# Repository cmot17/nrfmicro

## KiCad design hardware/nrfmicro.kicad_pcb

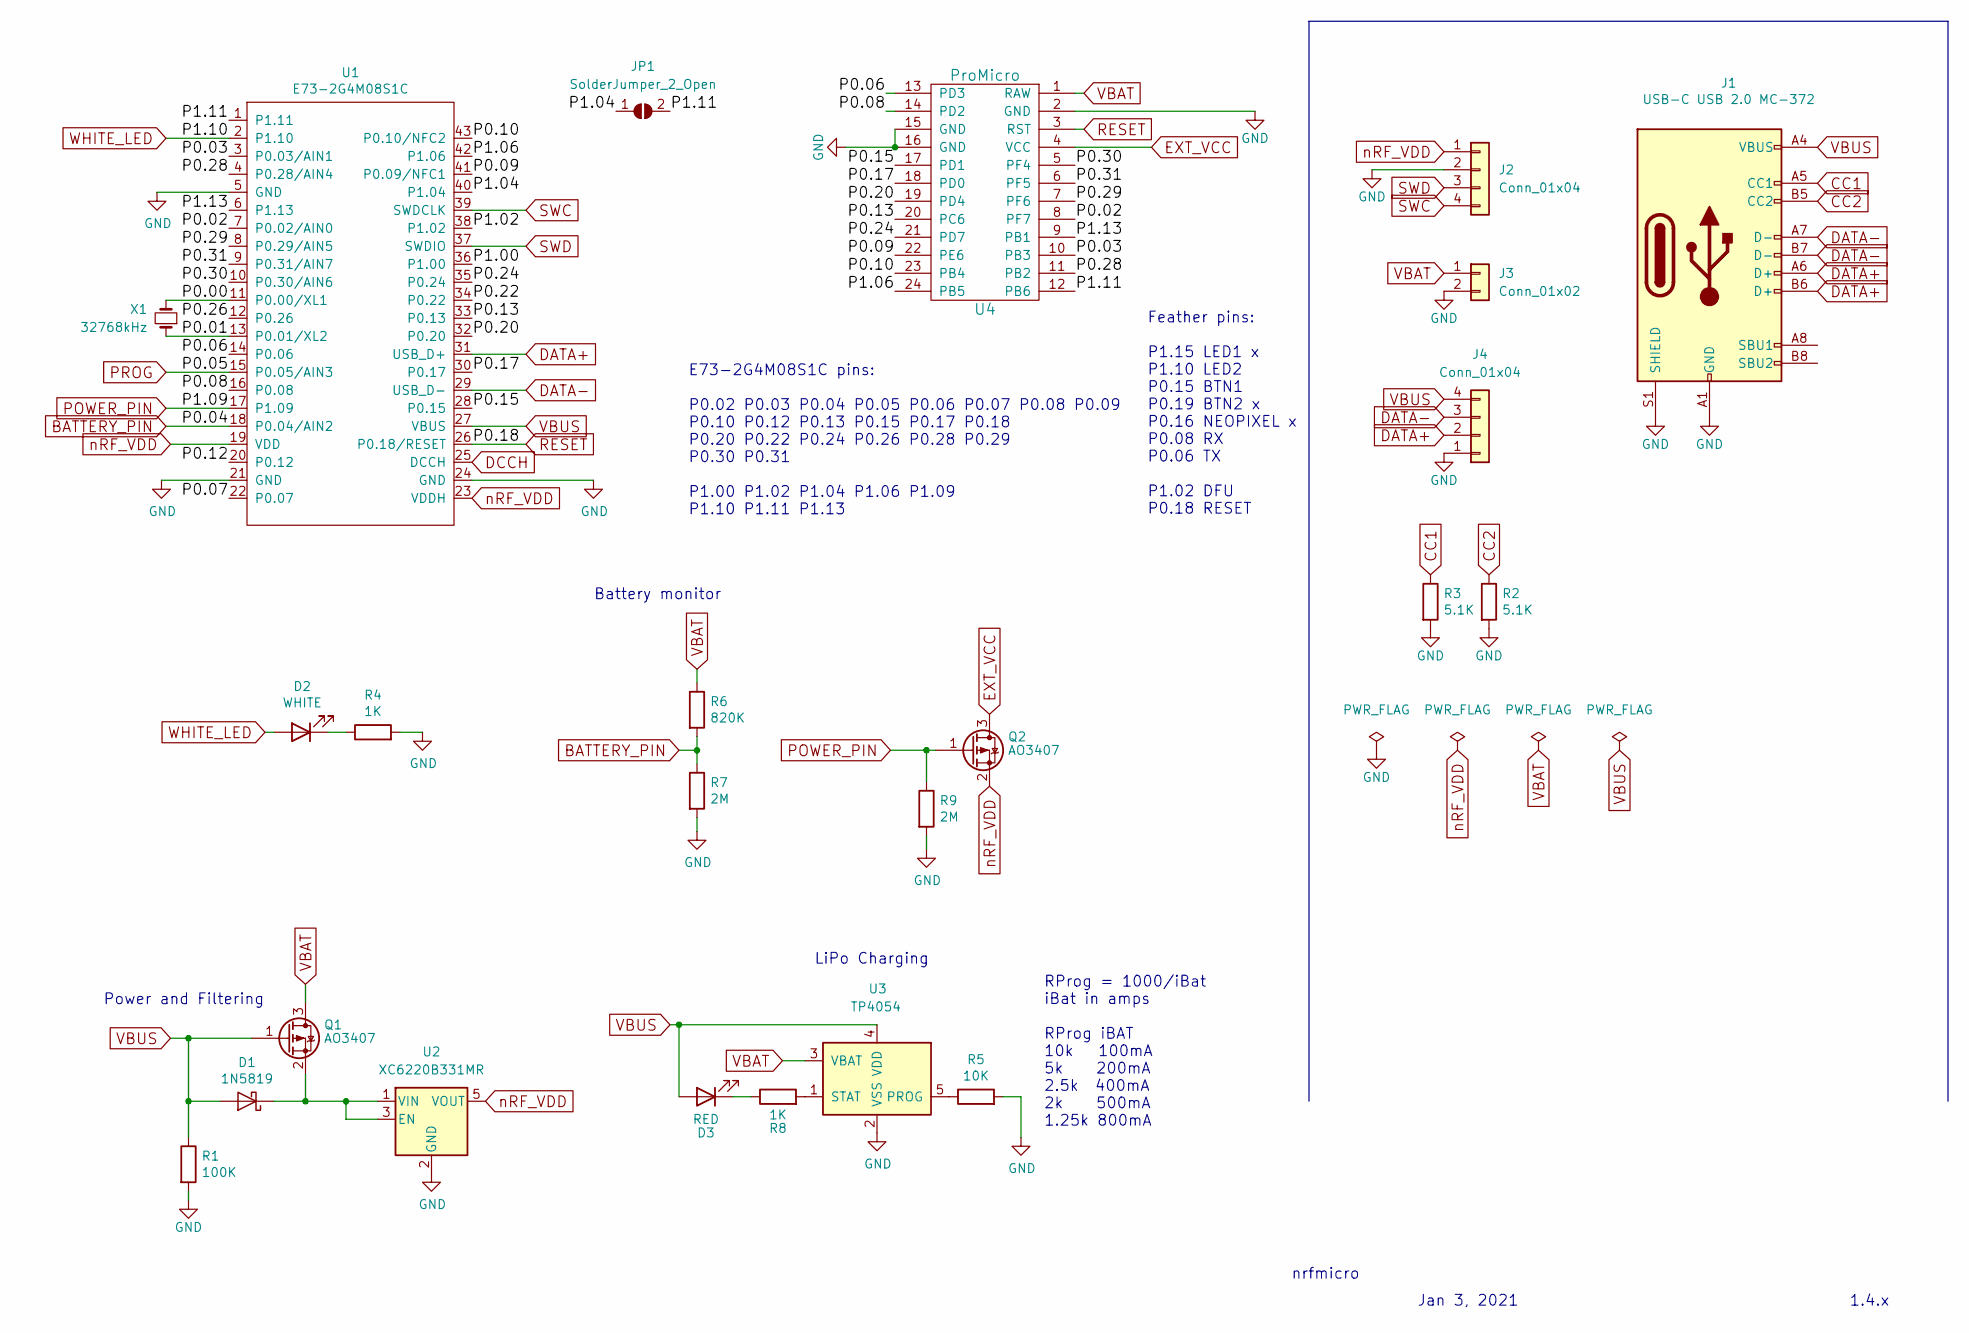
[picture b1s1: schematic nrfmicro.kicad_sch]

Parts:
D1: 1N5819; D_SOD-323F
D2: WHITE; LED_0603_1608Metric; LCSC C2290
D3: RED; LED_0603_1608Metric; LCSC C2286
J1: USB-C USB 2.0 MC-372; GT-USB-7047B; LCSC C963217
J2: Conn_01x04; connector_swd
J3: Conn_01x02; connector_bat
J4: Conn_01x04; connector_usb
JP1: SolderJumper_2_Open; Jumper_SMD
Q1, Q2: AO3407; SOT-23; JLCPCB Rotation Offset 180
R1: 100K; R_0402_1005Metric
R2, R3: 5.1K; R_0402_1005Metric
R4, R8: 1K; R_0402_1005Metric
R5: 10K; R_0402_1005Metric
R6: 820K; R_0402_1005Metric
R7, R9: 2M; R_0402_1005Metric
U1: E73-2G4M08S1C; E73-2G4M08S1C-52840
U2: XC6220B331MR; SOT-23-5; LCSC C86534
U3: TP4054; SOT-23-5; JLCPCB Rotation Offset 180
U4: ProMicro; pro_micro
X1: 32768kHz; Q13FC1350000400; LCSC C32346

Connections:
/P0.00: U1.11 (P0.00/XL1), X1.2
/P0.01: U1.13 (P0.01/XL2), X1.1
/P0.02: U1.7 (P0.02/AIN0), U4.8 (PF7)
/P0.03: U1.3 (P0.03/AIN1), U4.10 (PB3)
/P0.06: U1.14 (P0.06), U4.13 (PD3)
/P0.07: U1.22 (P0.07)
/P0.08: U1.16 (P0.08), U4.14 (PD2)
/P0.09: U1.41 (P0.09/NFC1), U4.22 (PE6)
/P0.10: U1.43 (P0.10/NFC2), U4.23 (PB4)
/P0.12: U1.20 (P0.12)
/P0.13: U1.33 (P0.13), U4.20 (PC6)
/P0.15: U1.28 (P0.15), U4.17 (PD1)
/P0.17: U1.30 (P0.17), U4.18 (PD0)
/P0.20: U1.32 (P0.20), U4.19 (PD4)
/P0.22: U1.34 (P0.22)
/P0.24: U1.35 (P0.24), U4.21 (PD7)
/P0.26: U1.12 (P0.26)
/P0.28: U1.4 (P0.28/AIN4), U4.11 (PB2)
/P0.29: U1.8 (P0.29/AIN5), U4.7 (PF6)
/P0.30: U1.10 (P0.30/AIN6), U4.5 (PF4)
/P0.31: U1.9 (P0.31/AIN7), U4.6 (PF5)
/P1.00: U1.36 (P1.00)
/P1.02: U1.38 (P1.02)
/P1.04: JP1.1 (A), U1.40 (P1.04)
/P1.06: U1.42 (P1.06), U4.24 (PB5)
/P1.11: JP1.2 (B), U1.1 (P1.11), U4.12 (PB6)
/P1.13: U1.6 (P1.13), U4.9 (PB1)
BATTERY_PIN: R6.2, R7.1, U1.18 (P0.04/AIN2)
CC1: J1.A5 (CC1), R3.1
CC2: J1.B5 (CC2), R2.1
DATA+: J1.A6 (D+), J1.B6 (D+), J4.2, U1.31 (USB_D+)
DATA-: J1.A7 (D-), J1.B7 (D-), J4.3, U1.29 (USB_D-)
DCCH: U1.25 (DCCH)
EXT_VCC: Q2.3 (D), U4.4 (VCC)
GND: J1.A1 (GND), J1.A12 (GND), J1.B1 (GND), J1.B12 (GND), J1.S1 (SHIELD), J2.2, J3.2, J4.1, R1.2, R2.2, R3.2, R4.2, R5.2, R7.2, R9.2, U1.5 (GND), U1.21 (GND), U1.24 (GND), U2.2 (GND), U3.2 (VSS), U4.2 (GND), U4.15 (GND), U4.16 (GND)
unnamed: D1.1 (K), Q1.2 (S), U2.1 (VIN), U2.3 (EN)
unnamed: D2.1 (K), R4.1
unnamed: D3.1 (K), R8.1
unnamed: R5.1, U3.5 (PROG)
unnamed: R8.2, U3.1 (STAT)
POWER_PIN: Q2.1 (G), R9.1, U1.17 (P1.09)
PROG: U1.15 (P0.05/AIN3)
RESET: U1.26 (P0.18/RESET), U4.3 (RST)
SWC: J2.4, U1.39 (SWDCLK)
SWD: J2.3, U1.37 (SWDIO)
VBAT: J3.1, Q1.3 (D), R6.1, U3.3 (VBAT), U4.1 (RAW)
VBUS: D1.2 (A), D3.2 (A), J1.A4 (VBUS), J1.A9 (VBUS), J1.B4 (VBUS), J1.B9 (VBUS), J4.4, Q1.1 (G), R1.1, U1.27 (VBUS), U3.4 (VDD)
WHITE_LED: D2.2 (A), U1.2 (P1.10)
nRF_VDD: J2.1, Q2.2 (S), U1.19 (VDD), U1.23 (VDDH), U2.5 (VOUT)

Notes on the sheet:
LiPo Charging
Jan 3, 2021
1.4.x
RProg = 1000/iBat iBat in amps RProg iBAT 10k 100mA 5k 200mA 2.5k 400mA 2k 500mA 1.25k 800mA
Power and Filtering
nrfmicro
Battery monitor
E73-2G4M08S1C pins: P0.02 P0.03 P0.04 P0.05 P0.06 P0.07 P0.08 P0.09 P0.10 P0.12 P0.13 P0.15 P0.17 P0.18 P0.20 P0.22 P0.24 P0.26 P0.28 P0.29 P0.30 P0.31 P1.00 P1.02 P1.04 P1.06 P1.09 P1.10 P1.11 P1.13
Feather pins: P1.15 LED1 x P1.10 LED2 P0.15 BTN1 P0.19 BTN2 x P0.16 NEOPIXEL x P0.08 RX P0.06 TX P1.02 DFU P0.18 RESET

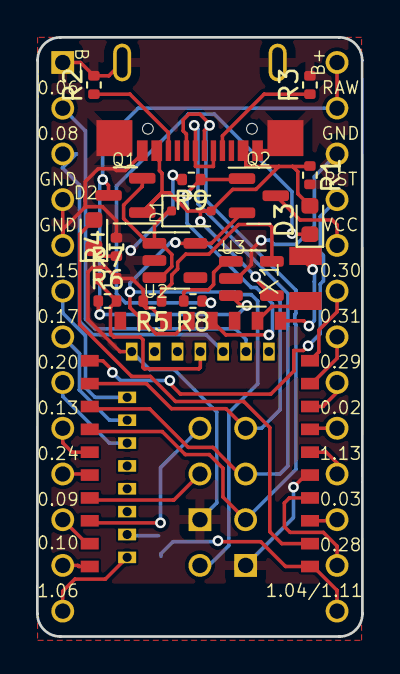
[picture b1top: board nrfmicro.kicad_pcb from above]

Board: 2 copper layers, 18.1 x 33.3 mm, 24 parts (1 on the bottom side), 41 nets.

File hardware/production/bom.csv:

Designator,Footprint,Quantity,Value,LCSC Part #
D1,D_SOD-323F,1,1N5819,
D2,0603,1,WHITE,C2290
D3,0603,1,RED,C2286
J1,GT-USB-7047B,1,USB-C USB 2.0 MC-372,C963217
JP1,Jumper_SMD,1,SolderJumper_2_Open,
"Q1, Q2",SOT-23,2,AO3407,
R1,0402,1,100K,
"R2, R3",0402,2,5.1K,
"R4, R8",0402,2,1K,
R5,0402,1,10K,
R6,0402,1,820K,
"R7, R9",0402,2,2M,
U1,E73-2G4M08S1C-52840,1,E73-2G4M08S1C,
U2,SOT-23-5,1,XC6220B331MR,C86534
U3,SOT-23-5,1,TP4054,
X1,Q13FC1350000400,1,32768kHz,C32346

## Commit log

2023-06-30 v0.1
